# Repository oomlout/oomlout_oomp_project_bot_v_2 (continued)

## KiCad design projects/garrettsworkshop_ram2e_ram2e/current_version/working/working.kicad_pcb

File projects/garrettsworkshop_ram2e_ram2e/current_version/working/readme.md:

# ram2e
 
## summary 
* id: garrettsworkshop_ram2e_ram2e
* user: garrettsworkshop
* name: ram2e
* board: ram2e
* repo: https://github.com/garrettsworkshop/RAM2E
* src_file_repo_kicad_pcb: RAM2E.kicad_pcb
* src_file_repo_kicad_pcb_link: https://github.com/garrettsworkshop/RAM2E/tree/release-GW4203B/RAM2E.kicad_pcb

* src_file_repo_sch: 
* src_file_repo_sch_link: https://github.com/garrettsworkshop/RAM2E/tree/release-GW4203B/
* full details link: https://github.com/oomlout/oomlout_oomp_project_bot_v_2/tree/main/projects/garrettsworkshop_ram2e_ram2e/current_version/working

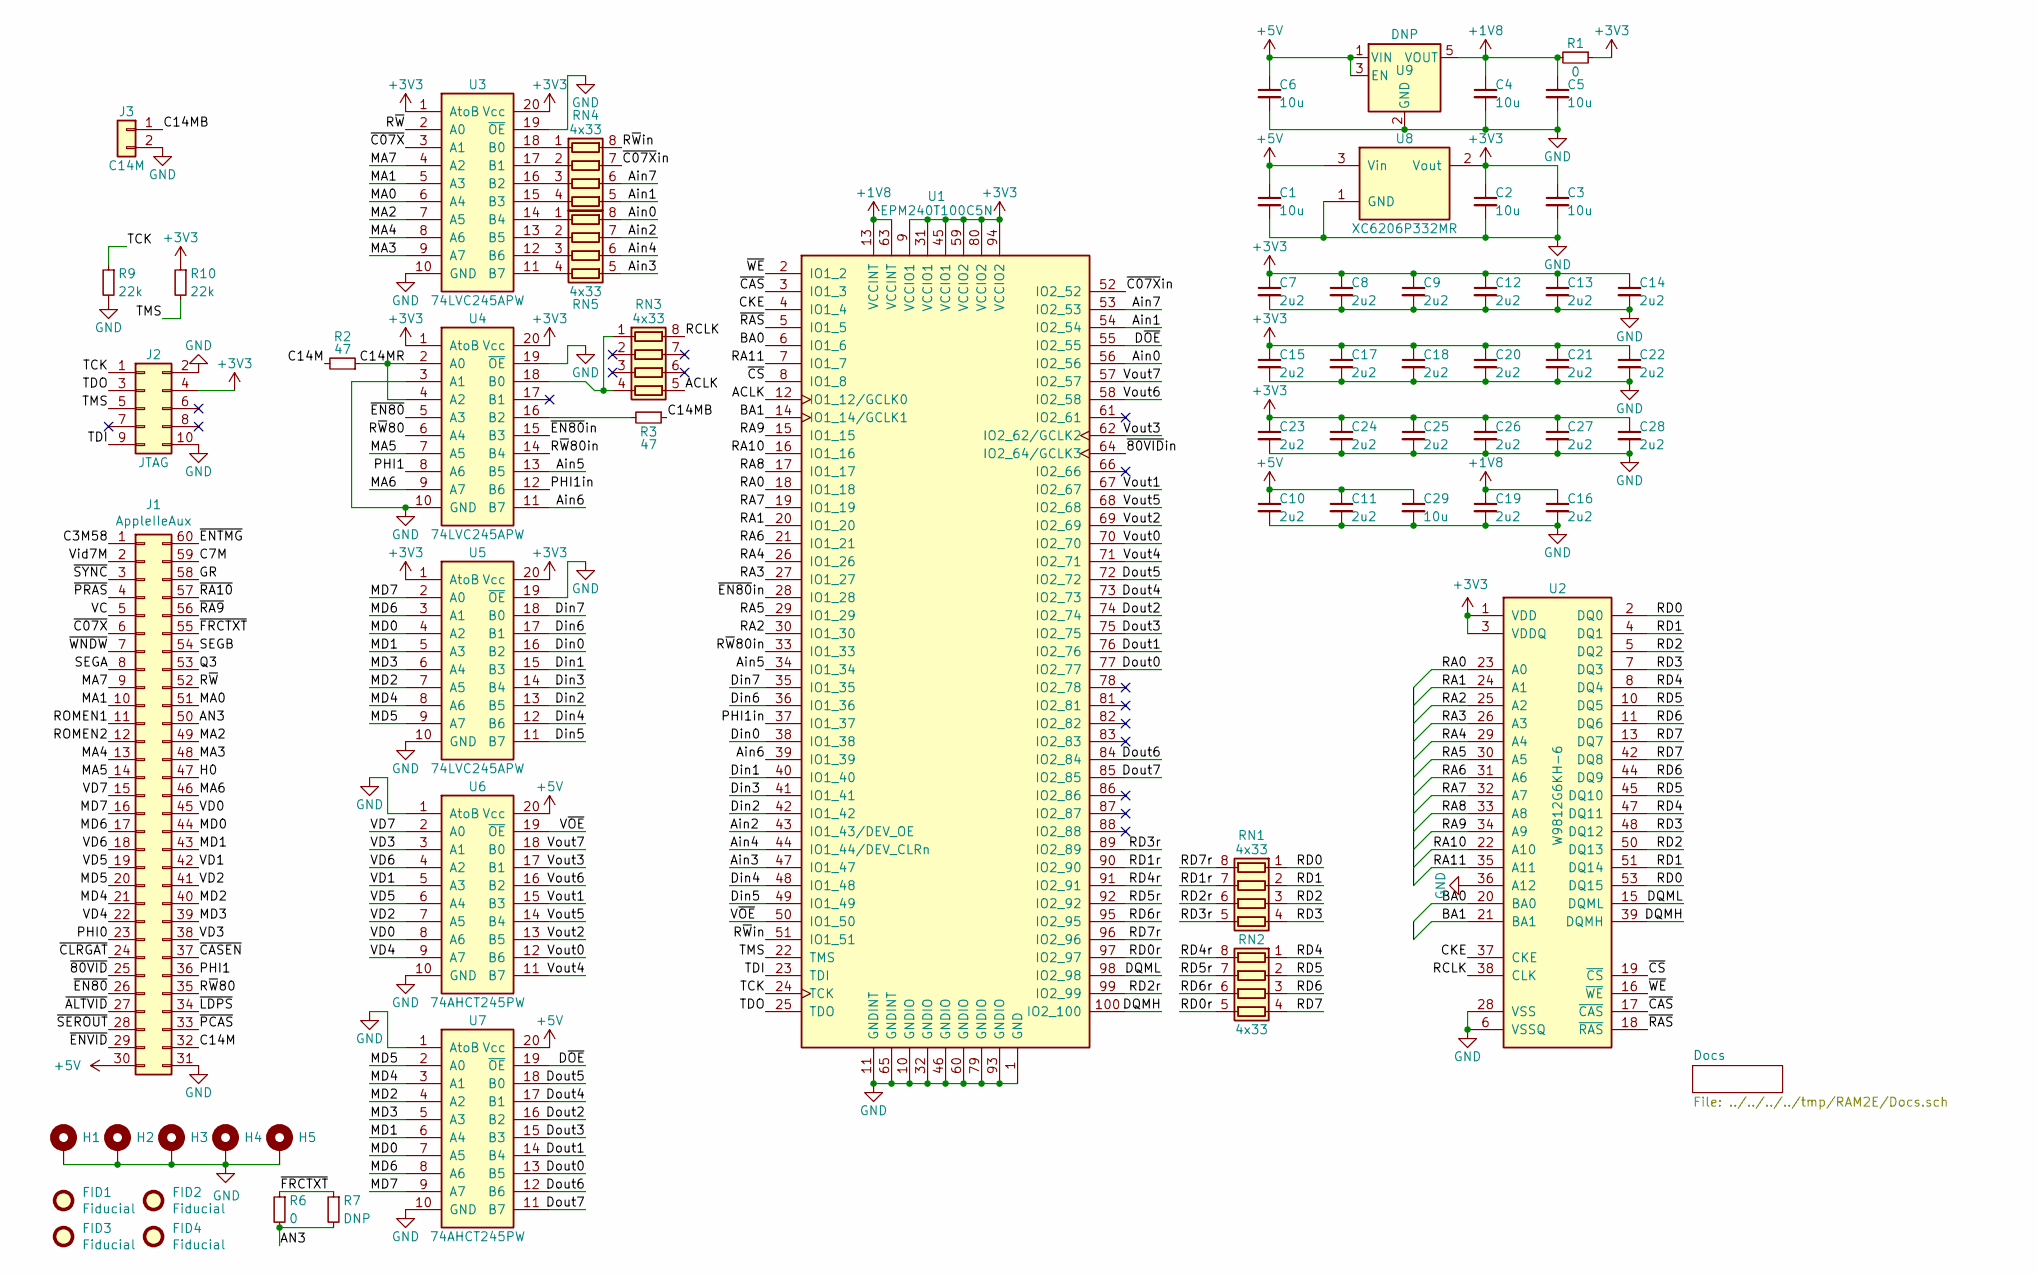
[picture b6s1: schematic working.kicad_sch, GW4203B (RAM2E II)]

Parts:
C1, C2, C3, C4, C5, C6, C29: 10u; C_0805; LCSC Part C15850
C7, C8, C9, C10, C11, C12, C13, C14, C15, C16, C17, C18, C19, C20, C21, C22, C23, C24, C25, C26, C27, C28: 2u2; C_0603; LCSC Part C23630
FID1, FID2, FID3, FID4: Fiducial
H1, H2, H3, H4: PasteHole_1.152mm_NPTH
H5: PasteHole_1.1mm_PTH
J1: AppleIIeAux; AppleIIeAux_Edge
J2: JTAG; TC2050
J3: C14M; PinHeader_1x02_P2.54mm_Vertical
R1, R6: 0; R_0805; LCSC Part C17477
R2, R3: 47; R_0603; LCSC Part C23182
R7: DNP; R_0805
R9, R10: 22k; R_0805; LCSC Part C17560
RN1, RN2, RN3, RN4, RN5: 4x33; R4_0402; LCSC Part C25501
U1: EPM240T100C5N; TQFP-100_14x14mm_P0.5mm; LCSC Part C10041
U2: W9812G6KH-6; TSOP-II-54_22.2x10.16mm_P0.8mm; LCSC Part C62379
U3, U4, U5: 74LVC245APW; TSSOP-20_4.4x6.5mm_P0.65mm; LCSC Part C6082
U6, U7: 74AHCT245PW; TSSOP-20_4.4x6.5mm_P0.65mm; LCSC Part C173388
U8: XC6206P332MR; SOT-23; LCSC Part C5446
U9: DNP; SOT-23-5

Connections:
+1V8: C4.1, C5.1, C16.1, C19.1, R1.2, U1.13 (VCCINT), U1.63 (VCCINT), U9.5 (VOUT)
+3V3: C2.1, C3.1, C7.1, C8.1, C9.1, C12.1, C13.1, C14.1, C15.1, C17.1, C18.1, C20.1, C21.1, C22.1, C23.1, C24.1, C25.1, C26.1, C27.1, C28.1, J2.4, R1.1, R10.1, U1.9 (VCCIO1), U1.31 (VCCIO1), U1.45 (VCCIO1), U1.59 (VCCIO2), U1.80 (VCCIO2), U1.94 (VCCIO2), U2.1 (VDD), U2.3 (VDDQ), U2.9 (VDDQ), U2.14 (VDD), U2.27 (VDD), U2.43 (VDDQ), U2.49 (VDDQ), U3.1 (AtoB), U3.20 (Vcc), U4.1 (AtoB), U4.20 (Vcc), U5.1 (AtoB), U5.20 (Vcc), U8.2 (Vout)
+5V: C1.1, C6.1, C10.1, C11.1, C29.1, J1.30, U6.20 (Vcc), U7.20 (Vcc), U8.3 (Vin), U9.1 (VIN), U9.3 (EN)
/ACLK: RN3.5 (R4.2), U1.12 (IO1_12/GCLK0)
/AN3: J1.50, R6.2, R7.2
/Ain0: RN5.8 (R1.2), U1.56 (IO2_56)
/Ain1: RN4.5 (R4.2), U1.54 (IO2_54)
/Ain2: RN5.7 (R2.2), U1.43 (IO1_43/DEV_OE)
/Ain3: RN5.5 (R4.2), U1.47 (IO1_47)
/Ain4: RN5.6 (R3.2), U1.44 (IO1_44/DEV_CLRn)
/Ain5: U1.34 (IO1_34), U4.13 (B5)
/Ain6: U1.39 (IO1_39), U4.11 (B7)
/Ain7: RN4.6 (R3.2), U1.53 (IO2_53)
/BA0: U1.6 (IO1_6), U2.20 (BA0)
/BA1: U1.14 (IO1_14/GCLK1), U2.21 (BA1)
/C3M58: J1.1
/C7M: J1.59
/C14M: J1.32, R2.2
/C14MB: J3.1, R3.1
/C14MR: R2.1, U4.2 (A0), U4.4 (A2)
/CKE: U1.4 (IO1_4), U2.37 (CKE)
/DQMH: U1.100 (IO2_100), U2.39 (DQMH)
/DQML: U1.98 (IO2_98), U2.15 (DQML)
/Din0: U1.38 (IO1_38), U5.16 (B2)
/Din1: U1.40 (IO1_40), U5.15 (B3)
/Din2: U1.42 (IO1_42), U5.13 (B5)
/Din3: U1.41 (IO1_41), U5.14 (B4)
/Din4: U1.48 (IO1_48), U5.12 (B6)
/Din5: U1.49 (IO1_49), U5.11 (B7)
/Din6: U1.36 (IO1_36), U5.17 (B1)
/Din7: U1.35 (IO1_35), U5.18 (B0)
/Dout0: U1.77 (IO2_77), U7.13 (B5)
/Dout1: U1.76 (IO2_76), U7.14 (B4)
/Dout2: U1.74 (IO2_74), U7.16 (B2)
/Dout3: U1.75 (IO2_75), U7.15 (B3)
/Dout4: U1.73 (IO2_73), U7.17 (B1)
/Dout5: U1.72 (IO2_72), U7.18 (B0)
/Dout6: U1.84 (IO2_84), U7.12 (B6)
/Dout7: U1.85 (IO2_85), U7.11 (B7)
/D~OE: U1.55 (IO2_55), U7.19 (~OE)
/GR: J1.58
/H0: J1.47
/MA0: J1.51, U3.6 (A4)
/MA1: J1.10, U3.5 (A3)
/MA2: J1.49, U3.7 (A5)
/MA3: J1.48, U3.9 (A7)
/MA4: J1.13, U3.8 (A6)
/MA5: J1.14, U4.7 (A5)
/MA6: J1.46, U4.9 (A7)
/MA7: J1.9, U3.4 (A2)
/MD0: J1.44, U5.4 (A2), U7.7 (A5)
/MD1: J1.43, U5.5 (A3), U7.6 (A4)
/MD2: J1.40, U5.7 (A5), U7.4 (A2)
/MD3: J1.39, U5.6 (A4), U7.5 (A3)
/MD4: J1.21, U5.8 (A6), U7.3 (A1)
/MD5: J1.20, U5.9 (A7), U7.2 (A0)
/MD6: J1.17, U5.3 (A1), U7.8 (A6)
/MD7: J1.16, U5.2 (A0), U7.9 (A7)
/PHI0: J1.23
/PHI1: J1.36, U4.8 (A6)
/PHI1in: U1.37 (IO1_37), U4.12 (B6)
/Q3: J1.53
/RA0: U1.18 (IO1_18), U2.23 (A0)
/RA1: U1.20 (IO1_20), U2.24 (A1)
/RA2: U1.30 (IO1_30), U2.25 (A2)
/RA3: U1.27 (IO1_27), U2.26 (A3)
/RA4: U1.26 (IO1_26), U2.29 (A4)
/RA5: U1.29 (IO1_29), U2.30 (A5)
/RA6: U1.21 (IO1_21), U2.31 (A6)
/RA7: U1.19 (IO1_19), U2.32 (A7)
/RA8: U1.17 (IO1_17), U2.33 (A8)
/RA9: U1.15 (IO1_15), U2.34 (A9)
/RA10: U1.16 (IO1_16), U2.22 (A10)
/RA11: U1.7 (IO1_7), U2.35 (A11)
/RCLK: RN3.8 (R1.2), U2.38 (CLK)
/RD0: RN1.1 (R1.1), U2.2 (DQ0), U2.53 (DQ15)
/RD0r: RN2.5 (R4.2), U1.97 (IO2_97)
/RD1: RN1.2 (R2.1), U2.4 (DQ1), U2.51 (DQ14)
/RD1r: RN1.7 (R2.2), U1.90 (IO2_90)
/RD2: RN1.3 (R3.1), U2.5 (DQ2), U2.50 (DQ13)
/RD2r: RN1.6 (R3.2), U1.99 (IO2_99)
/RD3: RN1.4 (R4.1), U2.7 (DQ3), U2.48 (DQ12)
/RD3r: RN1.5 (R4.2), U1.89 (IO2_89)
/RD4: RN2.1 (R1.1), U2.8 (DQ4), U2.47 (DQ11)
/RD4r: RN2.8 (R1.2), U1.91 (IO2_91)
/RD5: RN2.2 (R2.1), U2.10 (DQ5), U2.45 (DQ10)
/RD5r: RN2.7 (R2.2), U1.92 (IO2_92)
/RD6: RN2.3 (R3.1), U2.11 (DQ6), U2.44 (DQ9)
/RD6r: RN2.6 (R3.2), U1.95 (IO2_95)
/RD7: RN2.4 (R4.1), U2.13 (DQ7), U2.42 (DQ8)
/RD7r: RN1.8 (R1.2), U1.96 (IO2_96)
/ROMEN1: J1.11
/ROMEN2: J1.12
/R~W: J1.52, U3.2 (A0)
/R~W80: J1.35, U4.6 (A4)
/R~W80in: U1.33 (IO1_33), U4.14 (B4)
/R~Win: RN4.8 (R1.2), U1.51 (IO1_51)
/SEGA: J1.8
/SEGB: J1.54
/TCK: J2.1, R9.1, U1.24 (TCK)
/TDI: J2.9, U1.23 (TDI)
/TDO: J2.3, U1.25 (TDO)
/TMS: J2.5, R10.2, U1.22 (TMS)
/VC: J1.5
/VD0: J1.45, U6.8 (A6)
/VD1: J1.42, U6.5 (A3)
/VD2: J1.41, U6.7 (A5)
/VD3: J1.38, U6.3 (A1)
/VD4: J1.22, U6.9 (A7)
/VD5: J1.19, U6.6 (A4)
/VD6: J1.18, U6.4 (A2)
/VD7: J1.15, U6.2 (A0)
/Vid7M: J1.2
/Vout0: U1.70 (IO2_70), U6.12 (B6)
/Vout1: U1.67 (IO2_67), U6.15 (B3)
/Vout2: U1.69 (IO2_69), U6.13 (B5)
/Vout3: U1.62 (IO2_62/GCLK2), U6.17 (B1)
/Vout4: U1.71 (IO2_71), U6.11 (B7)
/Vout5: U1.68 (IO2_68), U6.14 (B4)
/Vout6: U1.58 (IO2_58), U6.16 (B2)
/Vout7: U1.57 (IO2_57), U6.18 (B0)
/V~OE: U1.50 (IO1_50), U6.19 (~OE)
/~80VID: J1.25
/~80VIDin: U1.64 (IO2_64/GCLK3)
/~ALTVID: J1.27
/~C07X: J1.6, U3.3 (A1)
/~C07Xin: RN4.7 (R2.2), U1.52 (IO2_52)
/~CASEN: J1.37
/~CAS: U1.3 (IO1_3), U2.17 (~CAS)
/~CLRGAT: J1.24
/~CS: U1.8 (IO1_8), U2.19 (~CS)
/~EN80: J1.26, U4.5 (A3)
/~EN80in: U1.28 (IO1_28), U4.15 (B3)
/~ENTMG: J1.60
/~ENVID: J1.29
/~FRCTXT: J1.55, R6.1, R7.1
/~LDPS: J1.34
/~PCAS: J1.33
/~PRAS: J1.4
/~RA9: J1.56
/~RA10: J1.57
/~RAS: U1.5 (IO1_5), U2.18 (~RAS)
/~SEROUT: J1.28
/~SYNC: J1.3
/~WE: U1.2 (IO1_2), U2.16 (~WE)
/~WNDW: J1.7
GND: C1.2, C2.2, C3.2, C4.2, C5.2, C6.2, C7.2, C8.2, C9.2, C10.2, C11.2, C12.2, C13.2, C14.2, C15.2, C16.2, C17.2, C18.2, C19.2, C20.2, C21.2, C22.2, C23.2, C24.2, C25.2, C26.2, C27.2, C28.2, C29.2, H1.1, H2.1, H3.1, H4.1, H5.1, J1.31, J2.2, J2.10, J3.2, R9.2, U1.1 (GND), U1.10 (GNDIO), U1.11 (GNDINT), U1.32 (GNDIO), U1.46 (GNDIO), U1.60 (GNDIO), U1.65 (GNDINT), U1.79 (GNDIO), U1.93 (GNDIO), U2.6 (VSSQ), U2.12 (VSSQ), U2.28 (VSS), U2.36 (A12), U2.41 (VSS), U2.46 (VSSQ), U2.52 (VSSQ), U2.54 (VSS), U3.10 (GND), U3.19 (~OE), U4.3 (A1), U4.10 (GND), U4.19 (~OE), U5.10 (GND), U5.19 (~OE), U6.1 (AtoB), U6.10 (GND), U7.1 (AtoB), U7.10 (GND), U8.1 (GND), U9.2 (GND)
unnamed: R3.2, U4.16 (B2)
unnamed: RN3.1 (R1.1), RN3.4 (R4.1), U4.18 (B0)
unnamed: RN4.1 (R1.1), U3.18 (B0)
unnamed: RN4.2 (R2.1), U3.17 (B1)
unnamed: RN4.3 (R3.1), U3.16 (B2)
unnamed: RN4.4 (R4.1), U3.15 (B3)
unnamed: RN5.1 (R1.1), U3.14 (B4)
unnamed: RN5.2 (R2.1), U3.13 (B5)
unnamed: RN5.3 (R3.1), U3.12 (B6)
unnamed: RN5.4 (R4.1), U3.11 (B7)

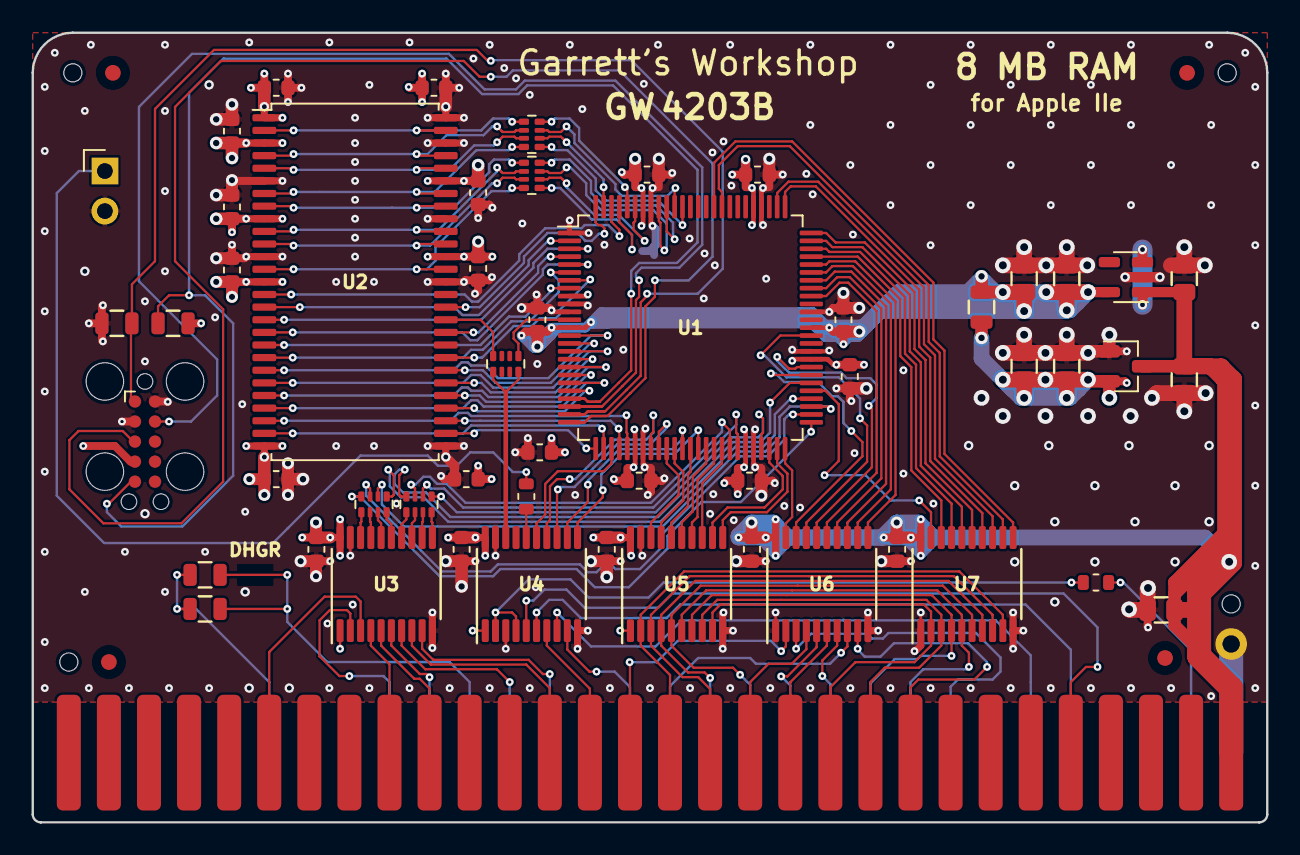
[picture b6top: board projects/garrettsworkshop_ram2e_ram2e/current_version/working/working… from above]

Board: 4 copper layers, 78.2 x 50.0 mm, 62 parts (0 on the bottom side), 130 nets.

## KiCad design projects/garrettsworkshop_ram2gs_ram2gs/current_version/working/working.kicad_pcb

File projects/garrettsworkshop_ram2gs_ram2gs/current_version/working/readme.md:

# ram2gs
 
## summary 
* id: garrettsworkshop_ram2gs_ram2gs
* user: garrettsworkshop
* name: ram2gs
* board: ram2gs
* repo: https://github.com/garrettsworkshop/RAM2GS
* src_file_repo_kicad_pcb: RAM2GS.kicad_pcb
* src_file_repo_kicad_pcb_link: https://github.com/garrettsworkshop/RAM2GS/tree/release-GW4201D/RAM2GS.kicad_pcb

* src_file_repo_sch: 
* src_file_repo_sch_link: https://github.com/garrettsworkshop/RAM2GS/tree/release-GW4201D/
* full details link: https://github.com/oomlout/oomlout_oomp_project_bot_v_2/tree/main/projects/garrettsworkshop_ram2gs_ram2gs/current_version/working

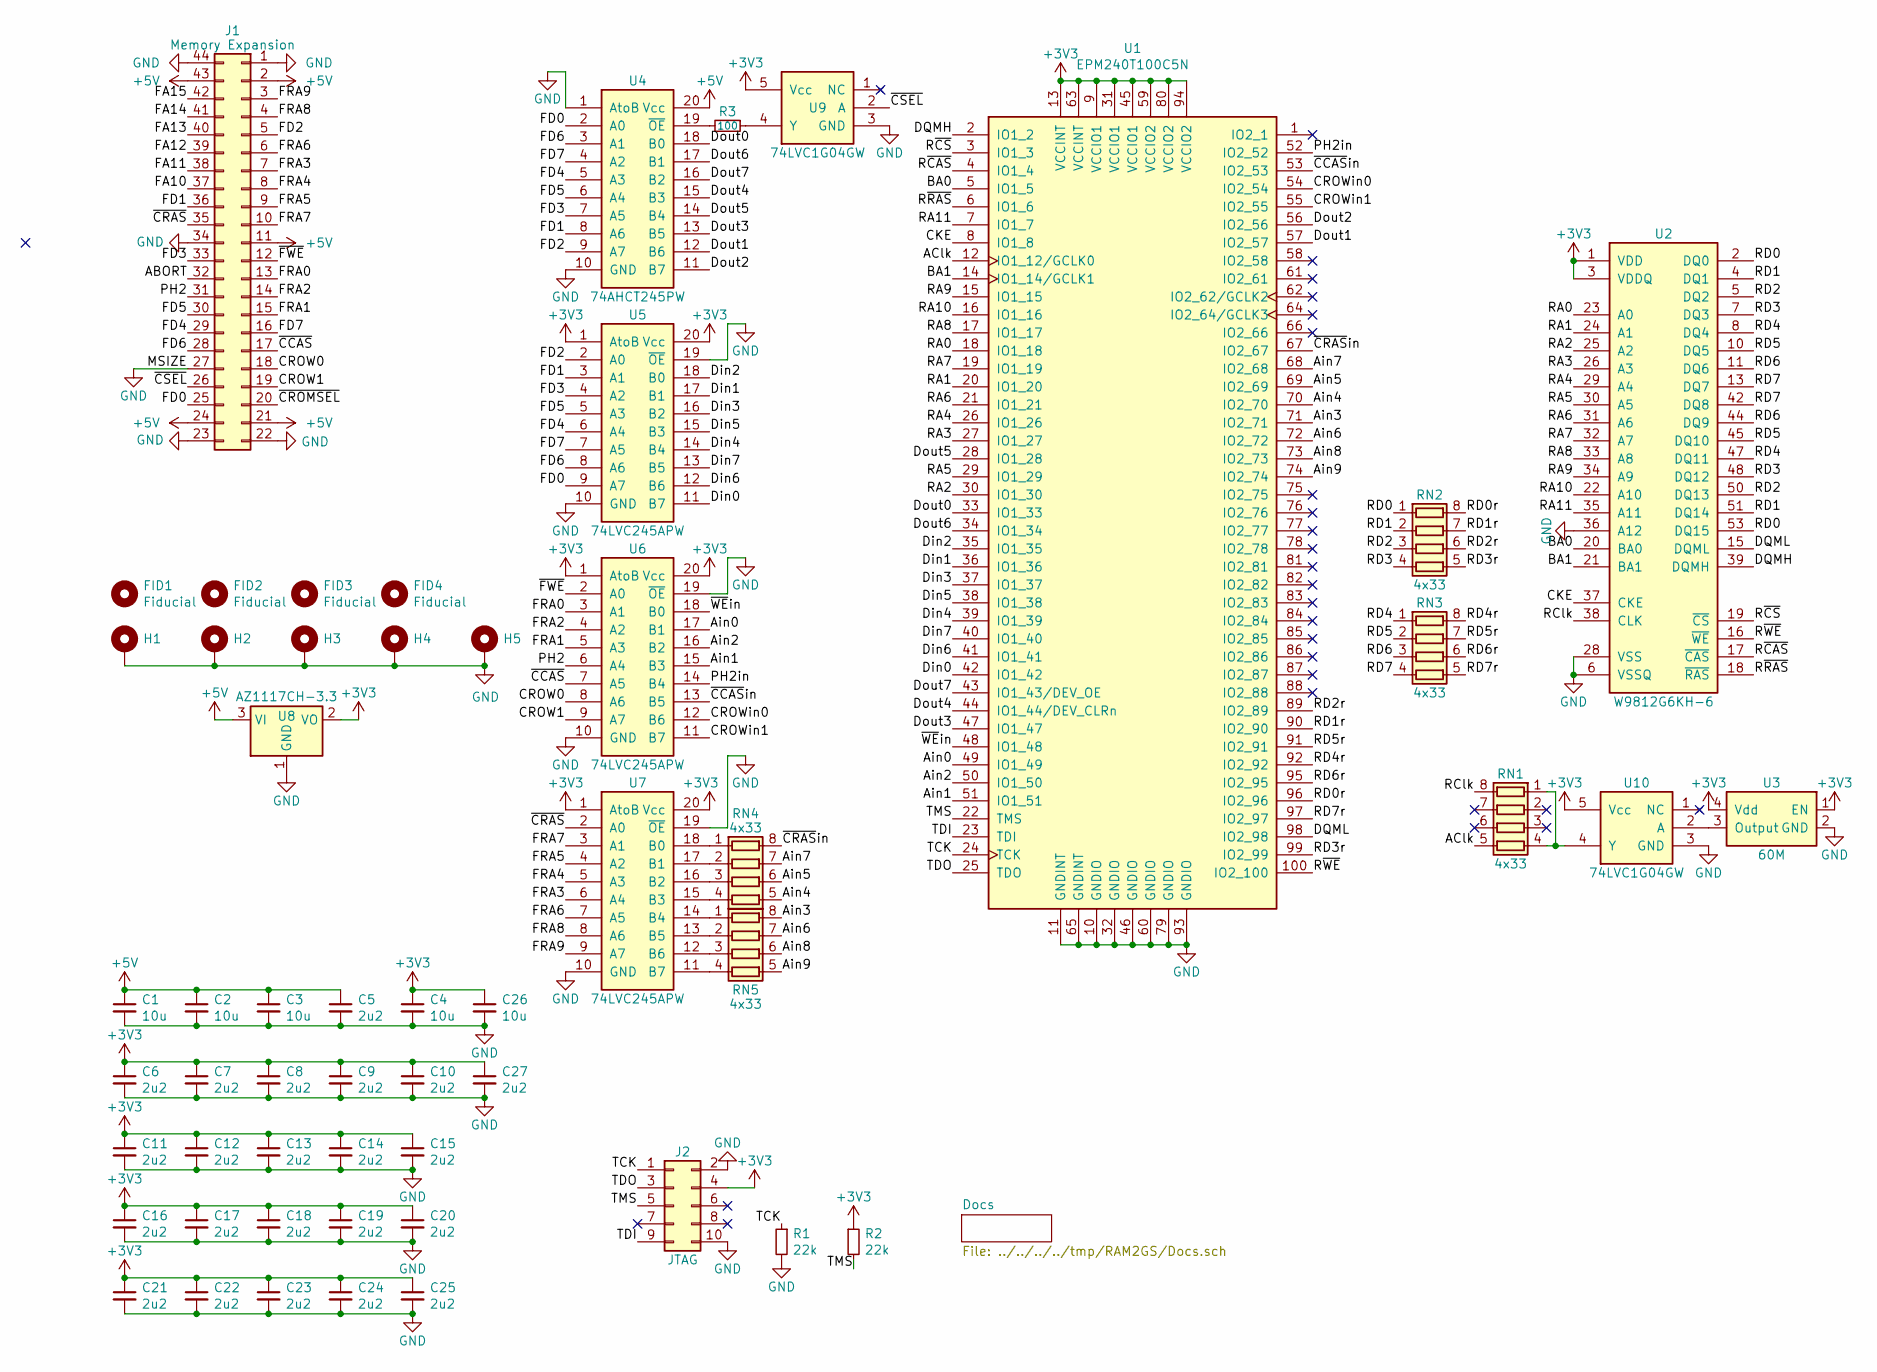
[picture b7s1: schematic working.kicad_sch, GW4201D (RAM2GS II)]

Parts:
C1, C2, C3, C4, C26: 10u; C_0805; LCSC Part C15850
C5, C6, C7, C8, C9, C10, C11, C12, C13, C14, C15, C16, C17, C18, C19, C20, C21, C22, C23, C24, C25, C27: 2u2; C_0603; LCSC Part C23630
FID1, FID2, FID3, FID4: Fiducial
H1, H2, H4, H5: PasteHole_1.152mm_NPTH
H3: PasteHole_1.1mm_PTH
J1: Memory Expansion; AppleIIgsMemoryExpansion_Edge
J2: JTAG; Tag-Connect_TC2050-IDC-FP_2x05_P1.27mm_Vertical
R1, R2: 22k; R_0805; LCSC Part C17560
R3: 100; R_0805; LCSC Part C17408
RN1, RN2, RN3, RN4, RN5: 4x33; R4_0402; LCSC Part C25501
U1: EPM240T100C5N; TQFP-100_14x14mm_P0.5mm; LCSC Part C10041
U2: W9812G6KH-6; TSOP-II-54_22.2x10.16mm_P0.8mm; LCSC Part C62379
U3: 60M; Crystal_SMD_7050-4Pin_7.0x5.0mm_SiTime; LCSC Part C26255
U4: 74AHCT245PW; TSSOP-20_4.4x6.5mm_P0.65mm; LCSC Part C173388
U5, U6, U7: 74LVC245APW; TSSOP-20_4.4x6.5mm_P0.65mm; LCSC Part C6082
U8: AZ1117CH-3.3; SOT-223; LCSC Part C92102
U9, U10: 74LVC1G04GW; SOT-353; LCSC Part C10237

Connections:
+3V3: C4.1, C6.1, C7.1, C8.1, C9.1, C10.1, C11.1, C12.1, C13.1, C14.1, C15.1, C16.1, C17.1, C18.1, C19.1, C20.1, C21.1, C22.1, C23.1, C24.1, C25.1, C26.1, C27.1, J2.4, R2.1, U1.9 (VCCIO1), U1.13 (VCCINT), U1.31 (VCCIO1), U1.45 (VCCIO1), U1.59 (VCCIO2), U1.63 (VCCINT), U1.80 (VCCIO2), U1.94 (VCCIO2), U2.1 (VDD), U2.3 (VDDQ), U2.9 (VDDQ), U2.14 (VDD), U2.27 (VDD), U2.43 (VDDQ), U2.49 (VDDQ), U3.1 (EN), U3.4 (Vdd), U5.1 (AtoB), U5.20 (Vcc), U6.1 (AtoB), U6.20 (Vcc), U7.1 (AtoB), U7.20 (Vcc), U8.2 (VO), U9.5 (Vcc), U10.5 (Vcc)
+5V: C1.1, C2.1, C3.1, C5.1, J1.2, J1.11, J1.21, J1.24, J1.43, U4.20 (Vcc), U8.3 (VI)
/ABORT: J1.32
/AClk: RN1.5 (R4.2), U1.12 (IO1_12/GCLK0)
/Ain0: U1.49 (IO1_49), U6.17 (B1)
/Ain1: U1.51 (IO1_51), U6.15 (B3)
/Ain2: U1.50 (IO1_50), U6.16 (B2)
/Ain3: RN5.8 (R1.2), U1.71 (IO2_71)
/Ain4: RN4.5 (R4.2), U1.70 (IO2_70)
/Ain5: RN4.6 (R3.2), U1.69 (IO2_69)
/Ain6: RN5.7 (R2.2), U1.72 (IO2_72)
/Ain7: RN4.7 (R2.2), U1.68 (IO2_68)
/Ain8: RN5.6 (R3.2), U1.73 (IO2_73)
/Ain9: RN5.5 (R4.2), U1.74 (IO2_74)
/BA0: U1.5 (IO1_5), U2.20 (BA0)
/BA1: U1.14 (IO1_14/GCLK1), U2.21 (BA1)
/CKE: U1.8 (IO1_8), U2.37 (CKE)
/CROW0: J1.18, U6.8 (A6)
/CROW1: J1.19, U6.9 (A7)
/CROWin0: U1.54 (IO2_54), U6.12 (B6)
/CROWin1: U1.55 (IO2_55), U6.11 (B7)
/DQMH: U1.2 (IO1_2), U2.39 (DQMH)
/DQML: U1.98 (IO2_98), U2.15 (DQML)
/Din0: U1.42 (IO1_42), U5.11 (B7)
/Din1: U1.36 (IO1_36), U5.17 (B1)
/Din2: U1.35 (IO1_35), U5.18 (B0)
/Din3: U1.37 (IO1_37), U5.16 (B2)
/Din4: U1.39 (IO1_39), U5.14 (B4)
/Din5: U1.38 (IO1_38), U5.15 (B3)
/Din6: U1.41 (IO1_41), U5.12 (B6)
/Din7: U1.40 (IO1_40), U5.13 (B5)
/Dout0: U1.33 (IO1_33), U4.18 (B0)
/Dout1: U1.57 (IO2_57), U4.12 (B6)
/Dout2: U1.56 (IO2_56), U4.11 (B7)
/Dout3: U1.47 (IO1_47), U4.13 (B5)
/Dout4: U1.44 (IO1_44/DEV_CLRn), U4.15 (B3)
/Dout5: U1.28 (IO1_28), U4.14 (B4)
/Dout6: U1.34 (IO1_34), U4.17 (B1)
/Dout7: U1.43 (IO1_43/DEV_OE), U4.16 (B2)
/FA10: J1.37
/FA11: J1.38
/FA12: J1.39
/FA13: J1.40
/FA14: J1.41
/FA15: J1.42
/FD0: J1.25, U4.2 (A0), U5.9 (A7)
/FD1: J1.36, U4.8 (A6), U5.3 (A1)
/FD2: J1.5, U4.9 (A7), U5.2 (A0)
/FD3: J1.33, U4.7 (A5), U5.4 (A2)
/FD4: J1.29, U4.5 (A3), U5.6 (A4)
/FD5: J1.30, U4.6 (A4), U5.5 (A3)
/FD6: J1.28, U4.3 (A1), U5.8 (A6)
/FD7: J1.16, U4.4 (A2), U5.7 (A5)
/FRA0: J1.13, U6.3 (A1)
/FRA1: J1.15, U6.5 (A3)
/FRA2: J1.14, U6.4 (A2)
/FRA3: J1.7, U7.6 (A4)
/FRA4: J1.8, U7.5 (A3)
/FRA5: J1.9, U7.4 (A2)
/FRA6: J1.6, U7.7 (A5)
/FRA7: J1.10, U7.3 (A1)
/FRA8: J1.4, U7.8 (A6)
/FRA9: J1.3, U7.9 (A7)
/PH2: J1.31, U6.6 (A4)
/PH2in: U1.52 (IO2_52), U6.14 (B4)
/RA0: U1.18 (IO1_18), U2.23 (A0)
/RA1: U1.20 (IO1_20), U2.24 (A1)
/RA2: U1.30 (IO1_30), U2.25 (A2)
/RA3: U1.27 (IO1_27), U2.26 (A3)
/RA4: U1.26 (IO1_26), U2.29 (A4)
/RA5: U1.29 (IO1_29), U2.30 (A5)
/RA6: U1.21 (IO1_21), U2.31 (A6)
/RA7: U1.19 (IO1_19), U2.32 (A7)
/RA8: U1.17 (IO1_17), U2.33 (A8)
/RA9: U1.15 (IO1_15), U2.34 (A9)
/RA10: U1.16 (IO1_16), U2.22 (A10)
/RA11: U1.7 (IO1_7), U2.35 (A11)
/RClk: RN1.8 (R1.2), U2.38 (CLK)
/RD0: RN2.1 (R1.1), U2.2 (DQ0), U2.53 (DQ15)
/RD0r: RN2.8 (R1.2), U1.96 (IO2_96)
/RD1: RN2.2 (R2.1), U2.4 (DQ1), U2.51 (DQ14)
/RD1r: RN2.7 (R2.2), U1.90 (IO2_90)
/RD2: RN2.3 (R3.1), U2.5 (DQ2), U2.50 (DQ13)
/RD2r: RN2.6 (R3.2), U1.89 (IO2_89)
/RD3: RN2.4 (R4.1), U2.7 (DQ3), U2.48 (DQ12)
/RD3r: RN2.5 (R4.2), U1.99 (IO2_99)
/RD4: RN3.1 (R1.1), U2.8 (DQ4), U2.47 (DQ11)
/RD4r: RN3.8 (R1.2), U1.92 (IO2_92)
/RD5: RN3.2 (R2.1), U2.10 (DQ5), U2.45 (DQ10)
/RD5r: RN3.7 (R2.2), U1.91 (IO2_91)
/RD6: RN3.3 (R3.1), U2.11 (DQ6), U2.44 (DQ9)
/RD6r: RN3.6 (R3.2), U1.95 (IO2_95)
/RD7: RN3.4 (R4.1), U2.13 (DQ7), U2.42 (DQ8)
/RD7r: RN3.5 (R4.2), U1.97 (IO2_97)
/R~CAS: U1.4 (IO1_4), U2.17 (~CAS)
/R~CS: U1.3 (IO1_3), U2.19 (~CS)
/R~RAS: U1.6 (IO1_6), U2.18 (~RAS)
/R~WE: U1.100 (IO2_100), U2.16 (~WE)
/TCK: J2.1, R1.1, U1.24 (TCK)
/TDI: J2.9, U1.23 (TDI)
/TDO: J2.3, U1.25 (TDO)
/TMS: J2.5, R2.2, U1.22 (TMS)
/~CCAS: J1.17, U6.7 (A5)
/~CCASin: U1.53 (IO2_53), U6.13 (B5)
/~CRAS: J1.35, U7.2 (A0)
/~CRASin: RN4.8 (R1.2), U1.67 (IO2_67)
/~CROMSEL: J1.20
/~CSEL: J1.26, U9.2 (A)
/~FWE: J1.12, U6.2 (A0)
/~WEin: U1.48 (IO1_48), U6.18 (B0)
GND: C1.2, C2.2, C3.2, C4.2, C5.2, C6.2, C7.2, C8.2, C9.2, C10.2, C11.2, C12.2, C13.2, C14.2, C15.2, C16.2, C17.2, C18.2, C19.2, C20.2, C21.2, C22.2, C23.2, C24.2, C25.2, C26.2, C27.2, H1.1, H2.1, H3.1, H4.1, H5.1, J1.1, J1.22, J1.23, J1.27, J1.34, J1.44, J2.2, J2.10, R1.2, U1.10 (GNDIO), U1.11 (GNDINT), U1.32 (GNDIO), U1.46 (GNDIO), U1.60 (GNDIO), U1.65 (GNDINT), U1.79 (GNDIO), U1.93 (GNDIO), U2.6 (VSSQ), U2.12 (VSSQ), U2.28 (VSS), U2.36 (A12), U2.41 (VSS), U2.46 (VSSQ), U2.52 (VSSQ), U2.54 (VSS), U3.2 (GND), U4.1 (AtoB), U4.10 (GND), U5.10 (GND), U5.19 (~OE), U6.10 (GND), U6.19 (~OE), U7.10 (GND), U7.19 (~OE), U8.1 (GND), U9.3 (GND), U10.3 (GND)
unnamed: R3.1, U9.4 (Y)
unnamed: R3.2, U4.19 (~OE)
unnamed: RN1.1 (R1.1), RN1.4 (R4.1), U10.4 (Y)
unnamed: RN4.1 (R1.1), U7.18 (B0)
unnamed: RN4.2 (R2.1), U7.17 (B1)
unnamed: RN4.3 (R3.1), U7.16 (B2)
unnamed: RN4.4 (R4.1), U7.15 (B3)
unnamed: RN5.1 (R1.1), U7.14 (B4)
unnamed: RN5.2 (R2.1), U7.13 (B5)
unnamed: RN5.3 (R3.1), U7.12 (B6)
unnamed: RN5.4 (R4.1), U7.11 (B7)
unnamed: U3.3 (Output), U10.2 (A)

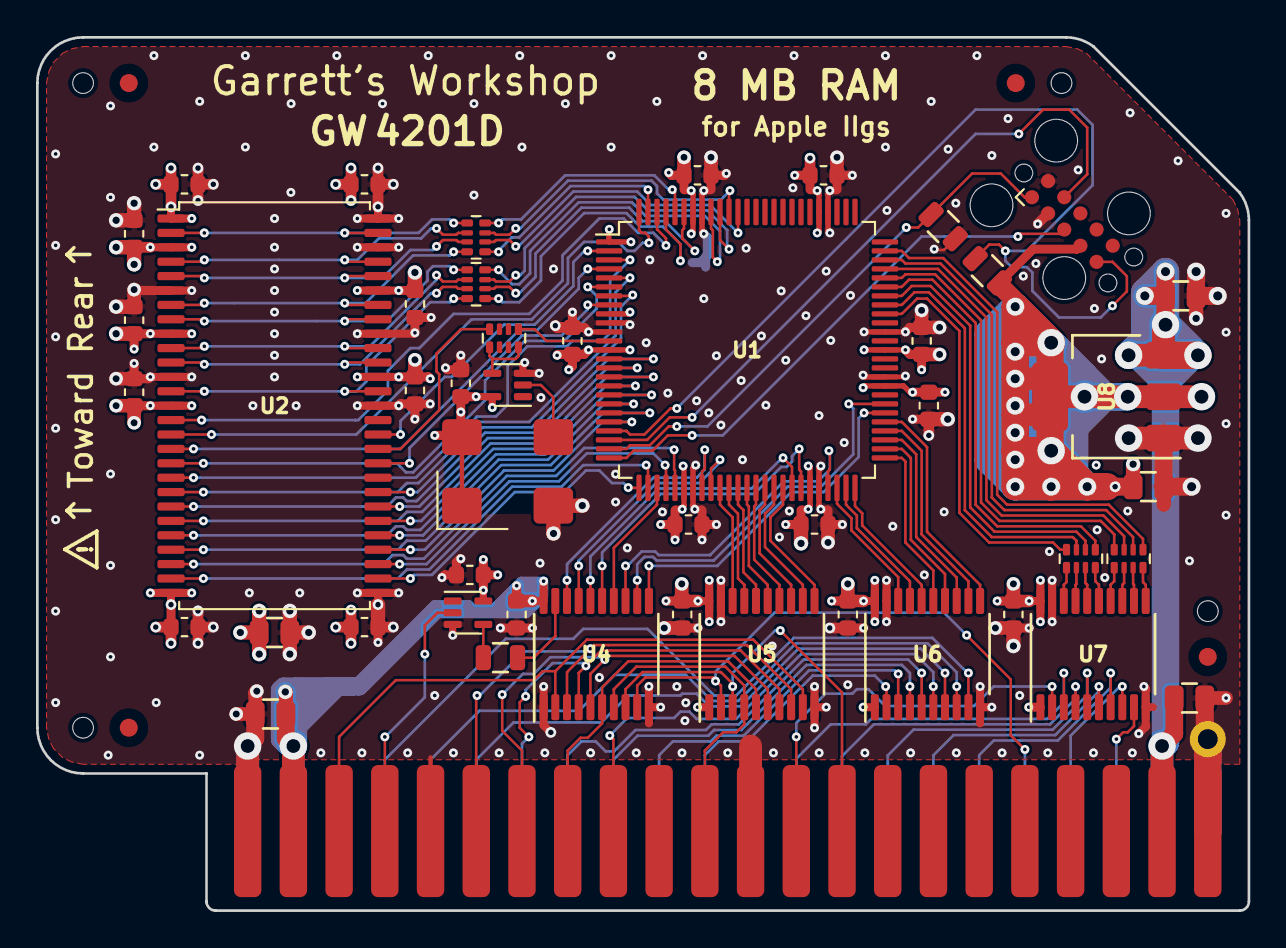
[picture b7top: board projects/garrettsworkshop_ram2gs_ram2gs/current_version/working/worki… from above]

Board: 4 copper layers, 67.3 x 48.5 mm, 56 parts (0 on the bottom side), 115 nets.
